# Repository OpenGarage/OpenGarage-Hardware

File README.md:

OpenGarage is a WiFi universal garage door opener based on the ESP8266 chip.

For details, visit [http://opengarage.io](http://opengarage.io)

This folder contains OpenGarage hardware design files, including:

* Schematic and Board files (EagleCAD)
* BOM, Pin assignments
* Enclosure design files
  - The original 3D design can be found at TinkerCad.com -> search for OpenGarage

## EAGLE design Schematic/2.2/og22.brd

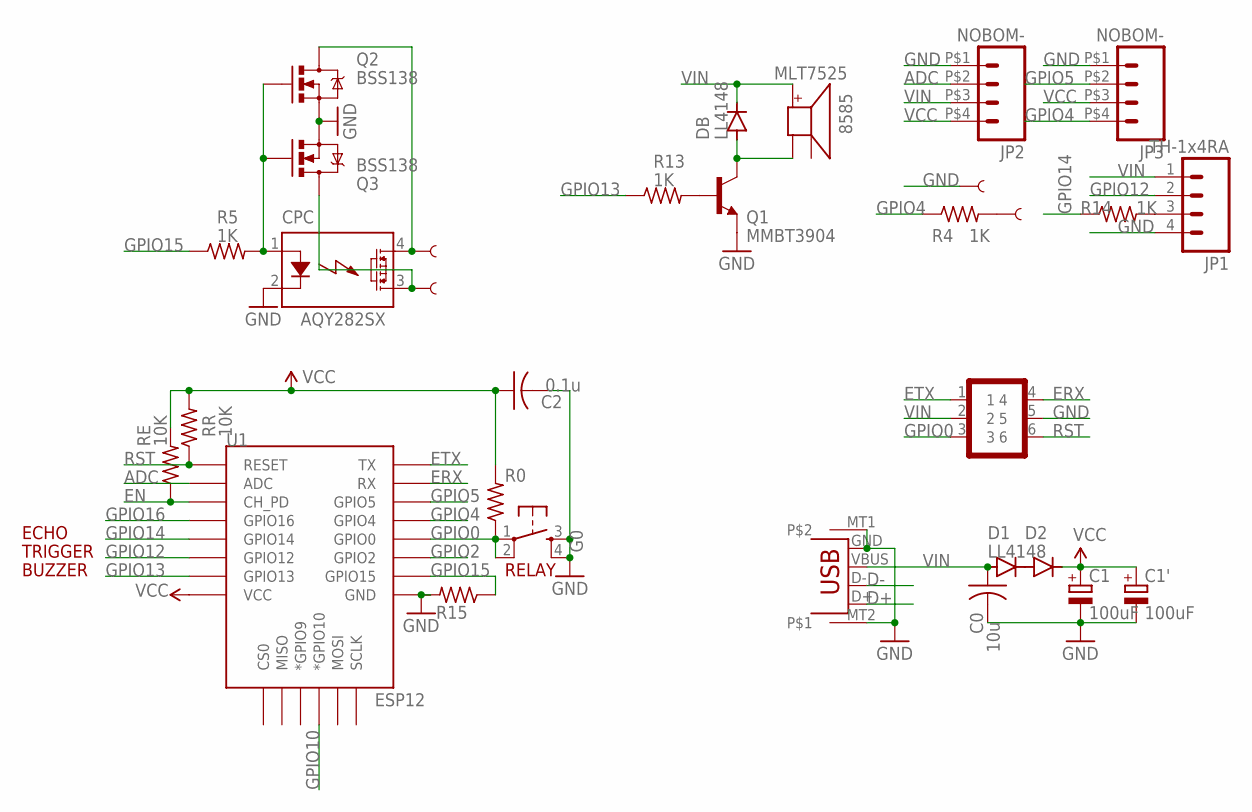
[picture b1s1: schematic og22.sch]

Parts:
8585: MLT7525; SMT-8585-BUZZER
C0: 10u; C0805K
C1, C1': 100uF; PANASONIC_C
C2: 0.1u; C0603K
CPC: AQY282SX; PHOTOMOS
D1, D2: LL4148; MINIMELF
DB: LL4148; MINIMELF
G0: TH-6x11; EVQ-Q2
JP1: TH-1x4RA; 1X04_SONICSENSOR_EXT2
JP2, JP3: NOBOM-; 1X04-2X2
Q1: MMBT3904; SOT23-3
Q2, Q3: BSS138; SOT23-3
R0, R15: 10K; R0603
R4, R5, R13, R14: 1K; R0603
RE: 10K; R0603
RR: 10K; R0603
U1: ESP12; ESP12E-SMD
U$1: NOBOM-GF2x3; GOLDFINGER_2X3
U$2, U$3, U$4, U$5: NOBOM-; PETAL-7MM-DOUBLE
X3: MICROXNJ; USB-MICROB2

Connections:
ADC: JP2.P$2 (2), U1.ADC
D+: X3.D+
D-: X3.D-
EN: RE.1, U1.CH_PD
ERX: U1.RXD0 (RX), U$1.4
ETX: U1.TXD0 (TX), U$1.1
GND: C0.2, C1.-, C1'.-, C2.2, CPC.2 (K), G0.3, G0.4, JP1.4, JP2.P$1 (1), JP3.P$1 (1), Q1.2 (E), Q2.2 (S), Q3.2 (S), R15.2, U1.GND, U$1.5, U$4.P$1, X3.GND, X3.MT1, X3.MT2
GPIO0: G0.1, G0.2, R0.1, U1.GPIO0, U$1.3
GPIO2: U1.GPIO2
GPIO4: JP3.P$4 (4), R4.1, U1.GPIO4
GPIO5: JP3.P$2 (2), U1.GPIO5
GPIO10: U1.GPIO10 (*GPIO10)
GPIO12: JP1.2, U1.GPIO12
GPIO13: R13.1, U1.GPIO13
GPIO14: R14.1, U1.GPIO14
GPIO15: R5.1, R15.1, U1.GPIO15
GPIO16: U1.GPIO16
unnamed: CPC.4 (DS1), Q2.3 (D), U$3.P$1
unnamed: CPC.3 (DS2), Q3.3 (D), U$2.P$1
unnamed: R4.2, U$5.P$1
unnamed: JP1.3, R14.2
unnamed: 8585.-, DB.A, Q1.3 (C)
unnamed: Q1.1 (B), R13.2
unnamed: CPC.1 (A), Q2.1 (G), Q3.1 (G), R5.2
unnamed: D1.C, D2.A
RST: RR.1, U1.RESET, U$1.6
VCC: C1.+, C1'.+, C2.1, D2.C, JP2.P$4 (4), JP3.P$3 (3), R0.2, RE.2, RR.2, U1.VCC
VIN: 8585.+, C0.1, D1.A, DB.C, JP1.1, JP2.P$3 (3), U$1.2, X3.VBUS

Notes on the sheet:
RELAY
BUZZER
ECHO
TRIGGER

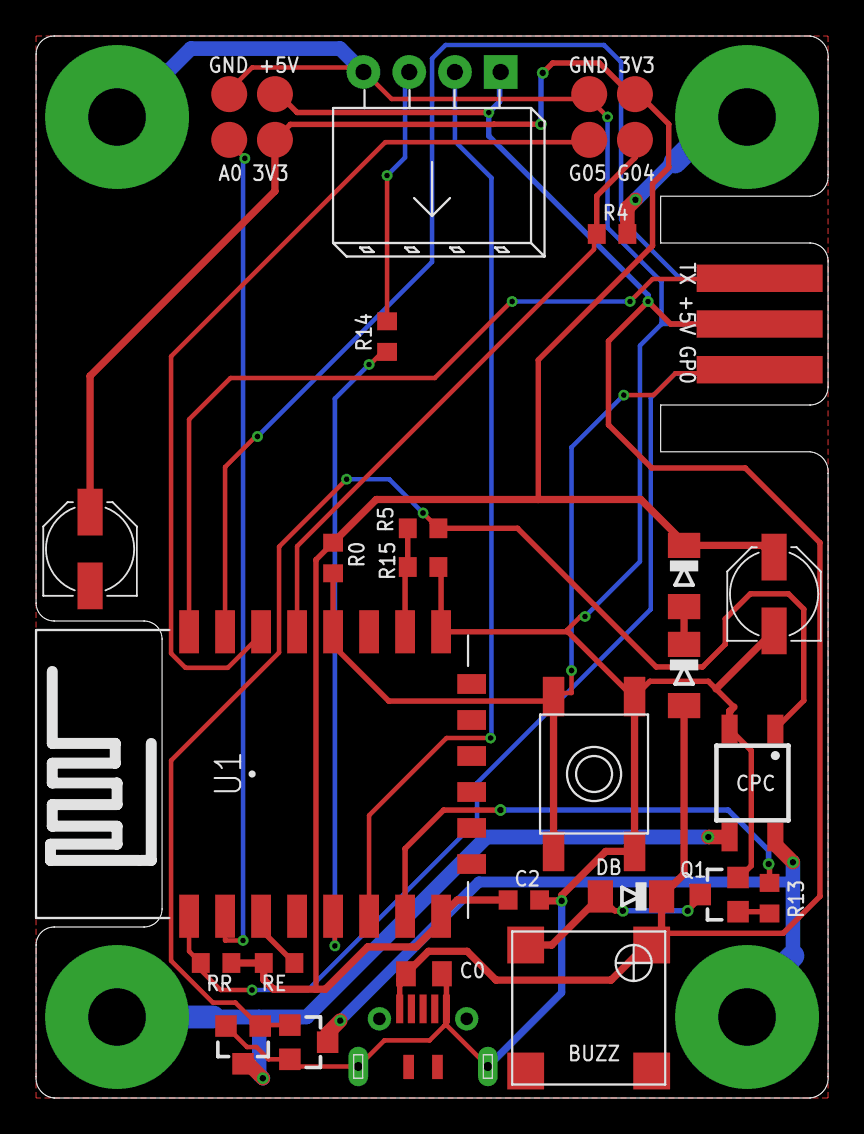
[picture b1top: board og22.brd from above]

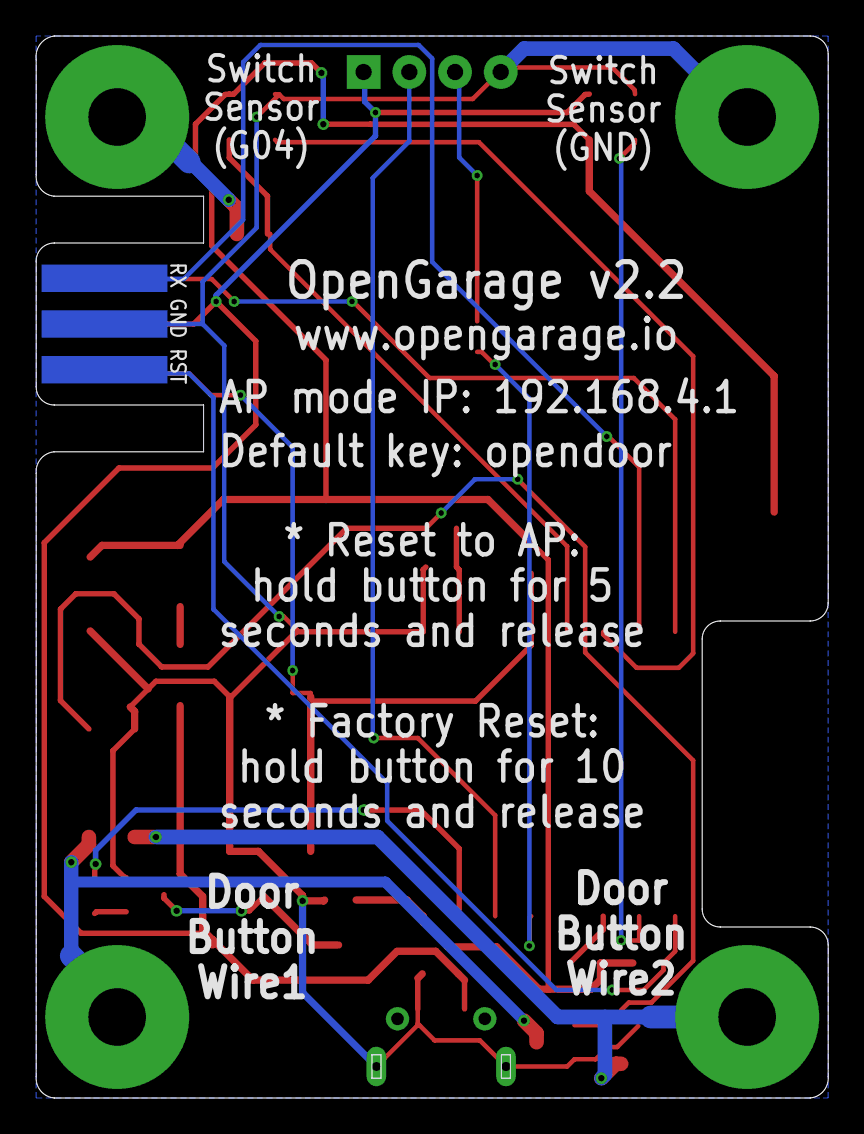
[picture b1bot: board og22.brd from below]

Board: 2 copper layers, 44.0 x 59.0 mm, 31 parts (4 on the bottom side), 23 nets.

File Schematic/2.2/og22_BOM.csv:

Name,Designator,Footprint,Quantity
0.1u,C2,C0603K,1
1K,"R4,R5,R13,R14",R0603,4
10K,"R0,R15,RE,RR",R0603,4
10u,C0,C0805K,1
100uF,"C1, C1'",PANASONIC_C,2
BSS138,Q2-3,SOT23-3,2
ESP12,U1,ESP12E-SMD,1
LL4148,"D1,D2,DB",MINIMELF,3
MICROXNJ,X3,USB-MICROB2,1
MLT7525,8585,SMT-8585-BUZZER,1
MMBT3904,Q1,SOT23-3,1
TH-1x4RA,JP1,1X04_SONICSENSOR_EXT2,1
TH-6x11,G0,EVQ-Q2,1

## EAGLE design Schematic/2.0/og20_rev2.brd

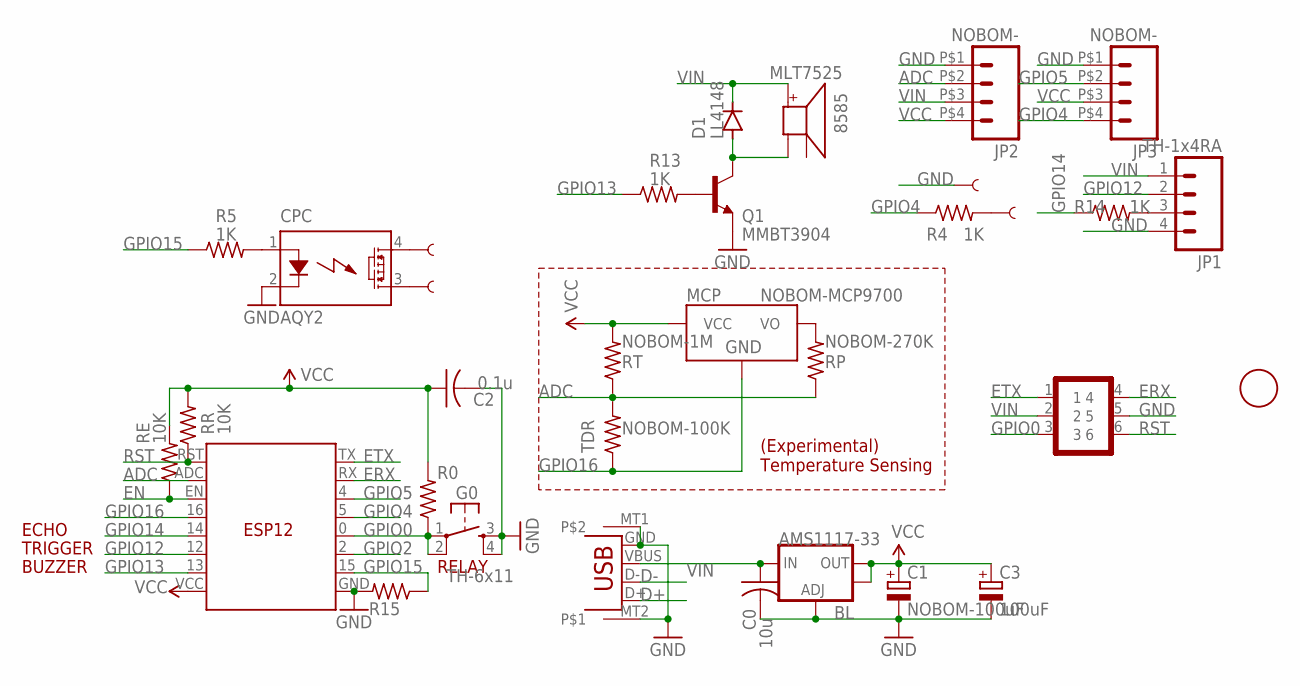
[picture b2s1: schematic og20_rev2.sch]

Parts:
0F: FIDUCIAL; FIDUCIAL_1MM
8585: MLT7525; SMT-8585-BUZZER
BL: AMS1117-33; SOT223
C0: 10u; C0805K
C1: NOBOM-100uF; B/3528-21R
C2: 0.1u; C0603K
C3: 100uF; PANASONIC_C
CPC: AQY2; PHOTOMOS
D1: LL4148; MINIMELF
ESP: ESP8266; ESP12
G0: TH-6x11; TACTILE-PTH
JP1: TH-1x4RA; 1X04_SONICSENSOR_EXT2
JP2, JP3: NOBOM-; 1X04-2X2
MCP: NOBOM-MCP9700; SOT23-3
Q1: MMBT3904; SOT23-3
R0, R15: 10K; R0603
R4, R5, R13, R14: 1K; R0603
RE: 10K; R0603
RP: NOBOM-270K; R0603
RR: 10K; R0603
RT: NOBOM-1M; R0603
TDR: NOBOM-100K; R0805
U$1: NOBOM-GF2x3; GOLDFINGER_2X3
U$2, U$3, U$4, U$5: NOBOM-; PETAL-3MM-1SIDE
X3: MICROXNJ; USB-MICROB2

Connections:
ADC: ESP.ADC, JP2.P$2 (2), RP.1, RT.1, TDR.2
D+: X3.D+
D-: X3.D-
EN: ESP.EN, RE.1
ERX: ESP.RX, U$1.4
ETX: ESP.TX, U$1.1
GND: BL.1 (ADJ), C0.2, C1.-, C2.2, C3.-, CPC.2 (K), ESP.GND, G0.3, G0.4, JP1.4, JP2.P$1 (1), JP3.P$1 (1), Q1.2 (E), R15.2, U$1.5, U$4.P$1, X3.GND, X3.MT1, X3.MT2
GPIO0: ESP.0 (G0), G0.1, G0.2, R0.1, U$1.3
GPIO2: ESP.2 (G2)
GPIO4: ESP.5 (G5), JP3.P$4 (4), R4.1
GPIO5: ESP.4 (G4), JP3.P$2 (2)
GPIO12: ESP.12 (G12), JP1.2
GPIO13: ESP.13 (G13), R13.1
GPIO14: ESP.14 (G14), R14.1
GPIO15: ESP.15 (G15), R5.1, R15.1
GPIO16: ESP.16 (G16), MCP.3 (GND), TDR.1
unnamed: CPC.4 (DS1), U$2.P$1
unnamed: CPC.3 (DS2), U$3.P$1
unnamed: R4.2, U$5.P$1
unnamed: JP1.3, R14.2
unnamed: 8585.-, D1.A, Q1.3 (C)
unnamed: MCP.2 (VO), RP.2
unnamed: Q1.1 (B), R13.2
unnamed: CPC.1 (A), R5.2
RST: ESP.RST, RR.1, U$1.6
VCC: BL.2 (OUT), BL.4 (OUT), C1.+, C2.1, C3.+, ESP.VCC, JP2.P$4 (4), JP3.P$3 (3), MCP.1 (VCC), R0.2, RE.2, RR.2, RT.2
VIN: 8585.+, BL.3 (IN), C0.1, D1.C, JP1.1, JP2.P$3 (3), U$1.2, X3.VBUS

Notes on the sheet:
RELAY
BUZZER
ECHO
TRIGGER
(Experimental) Temperature Sensing

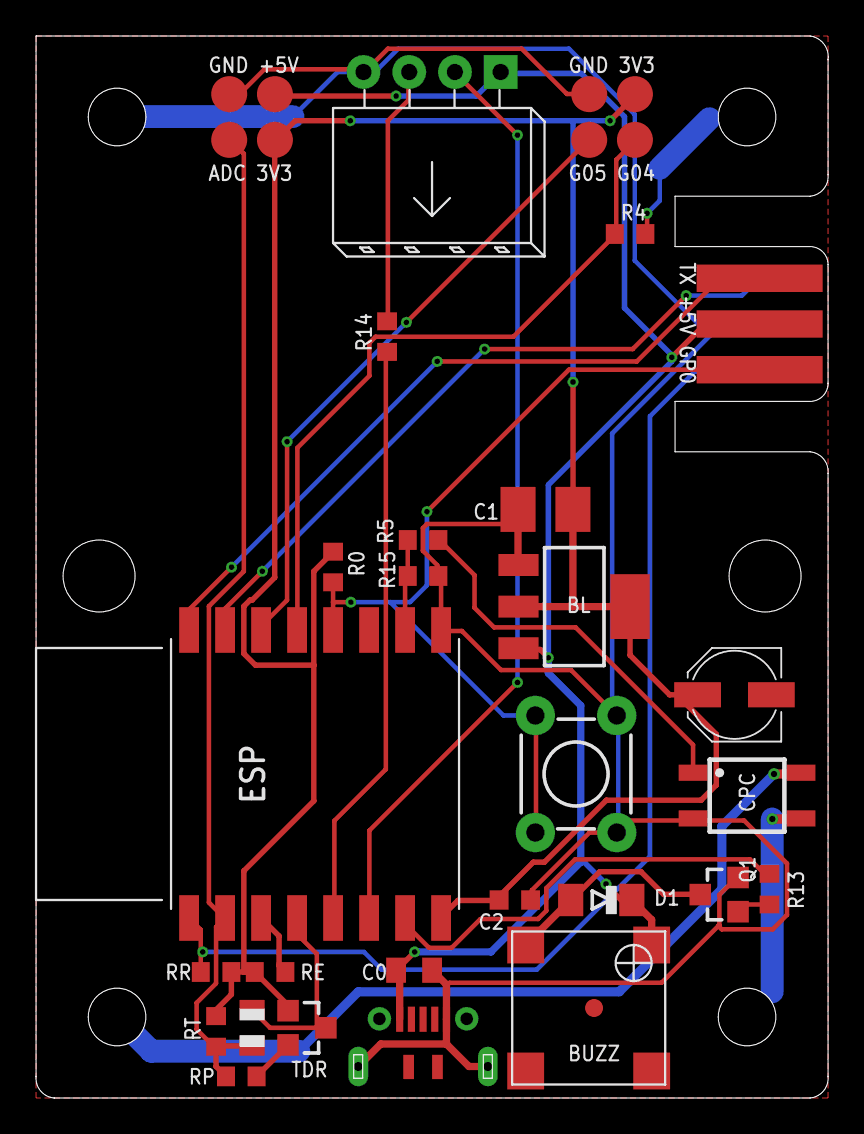
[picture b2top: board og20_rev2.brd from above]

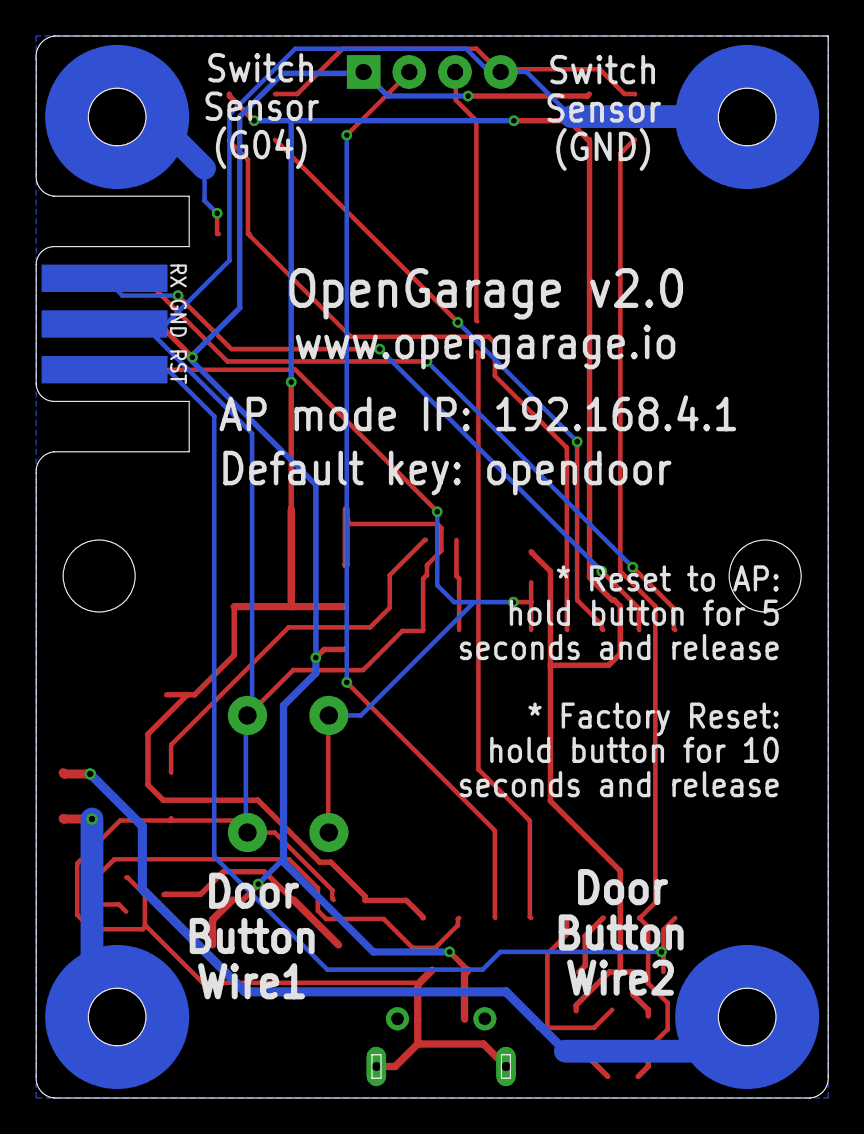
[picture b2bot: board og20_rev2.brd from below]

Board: 2 copper layers, 44.0 x 59.0 mm, 33 parts (4 on the bottom side), 24 nets.

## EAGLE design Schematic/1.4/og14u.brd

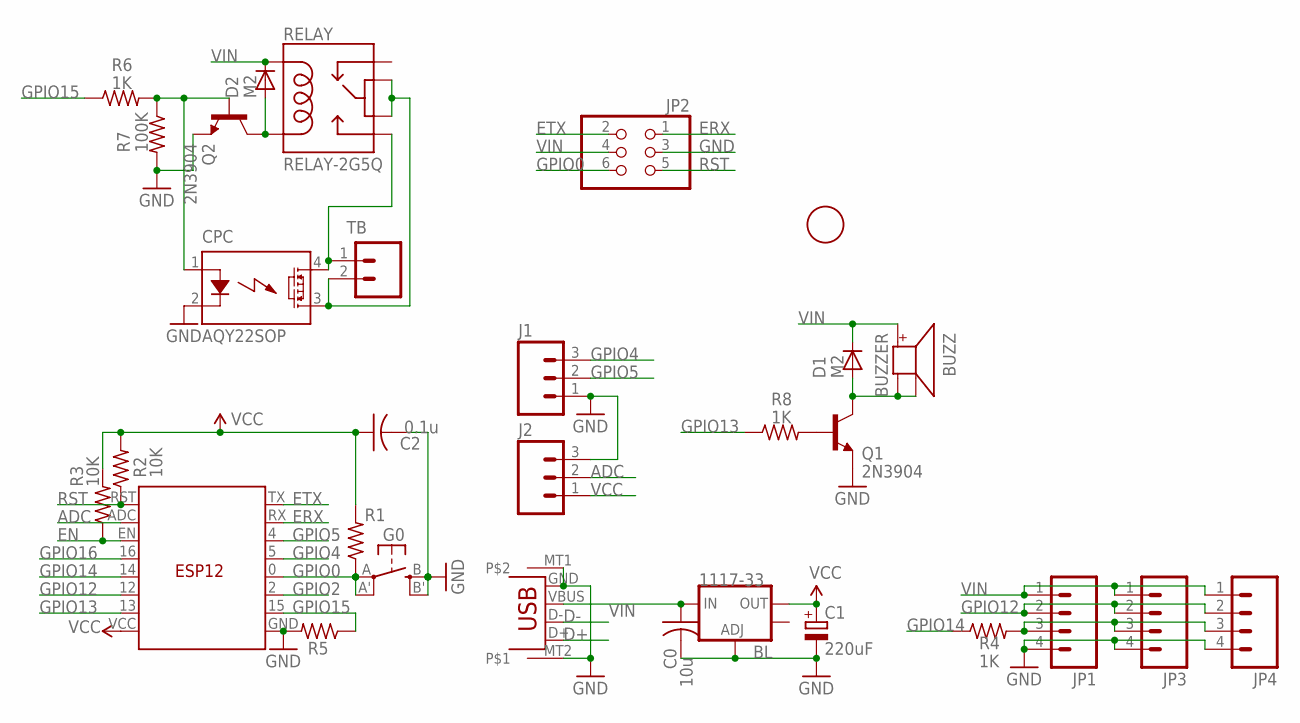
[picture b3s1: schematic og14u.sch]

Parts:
1F: FIDUCIAL; FIDUCIAL_1MM
BL: 1117-33; SOT223
BUZZ: BUZZER; SMT-8585-BUZZER
C0: 10u; C0805K
C1: 220uF; B/3528-21R
C2: 0.1u; C0603K
CPC: AQY22SOP; SOP04
D1, D2: M2; DO-214AC
ESP: ESP12
G0: SPST_TACT-EVQQ2; EVQ-Q2
J1, J2: M03PTH; 1X03
JP1: M04SONICSMD; 1X04_SONICSENSOR_SMD
JP2: PINHD-2X3; 2X03
JP3, JP4: M04DIST; 1X04_NO_SILK_DIST
Q1, Q2: 2N3904; SOT23-3
R1, R2, R3, R5: 10K; R0603
R4, R6, R8: 1K; R0603
R7: 100K; R0603
RELAY: RELAY-2G5Q; RELAY-G5V
TB: OPENER; SCREWTERMINAL-5MM-2-KF
X3: USB+GND; USB-MICROB2

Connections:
ADC: ESP.ADC, J2.2
D+: X3.D+
D-: X3.D-
EN: ESP.EN, R3.1
ERX: ESP.RX, JP2.1
ETX: ESP.TX, JP2.2
GND: BL.1 (ADJ), C0.2, C1.-, C2.2, CPC.2 (K), ESP.GND, G0.B (S), G0.B' (S1), J1.1, J2.3, JP1.4, JP2.3, JP3.4, JP4.4, Q1.2 (E), Q2.2 (E), R5.2, R7.2, X3.GND, X3.MT1, X3.MT2
GPIO0: ESP.0 (G0), G0.A, G0.A' (P1), JP2.6, R1.1
GPIO2: ESP.2 (G2)
GPIO4: ESP.5 (G5), J1.3
GPIO5: ESP.4 (G4), J1.2
GPIO12: ESP.12 (G12), JP1.2, JP3.2, JP4.2
GPIO13: ESP.13 (G13), R8.1
GPIO14: ESP.14 (G14), R4.1
GPIO15: ESP.15 (G15), R5.1, R6.1
GPIO16: ESP.16 (G16)
unnamed: CPC.4 (DS1), RELAY.10, TB.1
unnamed: CPC.3 (DS2), RELAY.5, RELAY.6, TB.2
unnamed: JP1.3, JP3.3, JP4.3, R4.2
unnamed: BUZZ.-, BUZZ.A-, D1.A, Q1.3 (C)
unnamed: Q1.1 (B), R8.2
unnamed: D2.A, Q2.3 (C), RELAY.9
unnamed: CPC.1 (A), Q2.1 (B), R6.2, R7.1
RST: ESP.RST, JP2.5, R2.1
VCC: BL.2 (OUT), C1.+, C2.1, ESP.VCC, J2.1, R1.2, R2.2, R3.2
VIN: BL.3 (IN), BUZZ.+, C0.1, D1.C, D2.C, JP1.1, JP2.4, JP3.1, JP4.1, RELAY.2, X3.VBUS

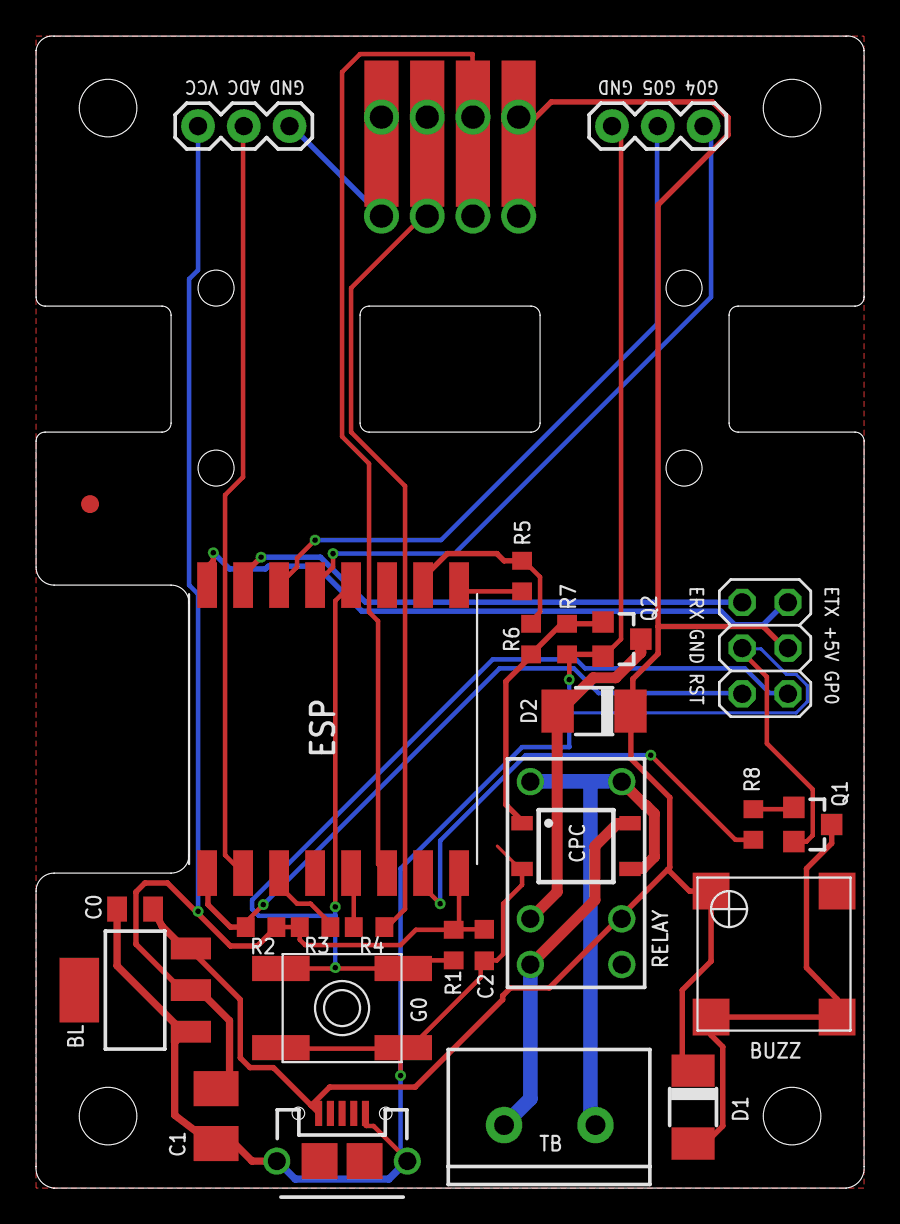
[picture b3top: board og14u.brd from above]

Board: 2 copper layers, 46.0 x 64.0 mm, 30 parts (0 on the bottom side), 22 nets.

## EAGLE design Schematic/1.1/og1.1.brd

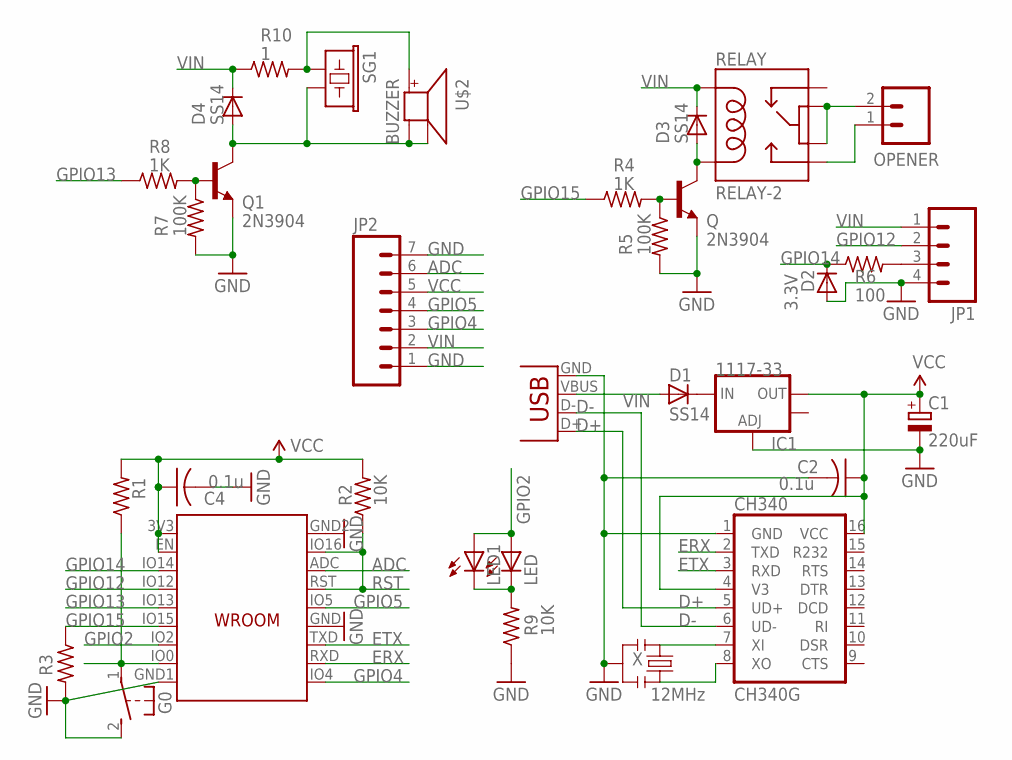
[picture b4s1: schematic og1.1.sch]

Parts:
C1: 220uF; CT3528
C2, C4: 0.1u; C0603K
CH340: CH340G; SO16
D1, D3, D4: SS14; DO-214AC
D2: 3.3V; MINIMELF
ESP: WROOM02; WROOM
G0: 31-XX; B3F-31XX
IC1: 1117-33; SOT223
JP1: M04SONIC; 1X04_SONICSENSOR
JP2: M07; 1X07
LED: LEDLED3MM_ABBRV; LED3MM_ABBRV
LED1: LEDCHIPLED_0805; CHIPLED_0805
OPENER: OPENER; SCREWTERMINAL-4MM-2-X
Q, Q1: 2N3904; SOT23-3
R1, R2, R3, R9: 10K; R0603
R4, R8: 1K; R0603
R5, R7: 100K; R0603
R6: 100; R0603
R10: 1; R0603
RELAY: RELAY-2; RELAY-HK4100F
SG1: BUZZERPTH; BUZZER-12MM
U$2: BUZZER; SMT-8585-BUZZER
X: 12MHz; RESONATOR-SMD
X3: USB-MICROB

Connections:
ADC: ESP.ADC, JP2.6
D+: CH340.5 (UD+), X3.D+
D-: CH340.6 (UD-), X3.D-
ERX: CH340.2 (TXD), ESP.RXD (RX)
ETX: CH340.3 (RXD), ESP.TXD (TX)
GND: C1.-, C2.2, C4.2, CH340.1 (GND), D2.A, ESP.GND, ESP.GND1, ESP.GND2, G0.2 (S), IC1.1 (ADJ), JP1.4, JP2.1, JP2.7, Q.2 (E), Q1.2 (E), R3.2, R5.2, R7.2, R9.1, X.2, X3.GND
GPIO0: ESP.IO0, G0.1, R1.1
GPIO2: ESP.IO2, LED.A, LED1.A
GPIO4: ESP.IO4, JP2.3
GPIO5: ESP.IO5, JP2.4
GPIO12: ESP.IO12, JP1.2
GPIO13: ESP.IO13, R8.1
GPIO14: D2.C, ESP.IO14, R6.1
GPIO15: ESP.IO15, R3.1, R4.1
unnamed: D1.C, IC1.3 (IN)
unnamed: Q.1 (B), R4.2, R5.1
unnamed: OPENER.2, RELAY.5, RELAY.6
unnamed: OPENER.1, RELAY.10
unnamed: JP1.3, R6.2
unnamed: D4.A, Q1.3 (C), SG1.- (2), U$2.-, U$2.A-
unnamed: LED.K (C), LED1.C, R9.2
unnamed: Q1.1 (B), R7.1, R8.2
unnamed: R10.2, SG1.+ (1), U$2.+
unnamed: CH340.7 (XI), X.1
unnamed: CH340.8 (XO), X.3
unnamed: D3.A, Q.3 (C), RELAY.9
RST: ESP.IO16, ESP.RST, R2.1
VCC: C1.+, C2.1, C4.1, CH340.4 (V3), CH340.16 (VCC), ESP.3V3 (VCC), ESP.EN, IC1.2 (OUT), JP2.5, R1.2, R2.2
VIN: D1.A, D3.C, D4.C, JP1.1, JP2.2, R10.1, RELAY.2, X3.VBUS

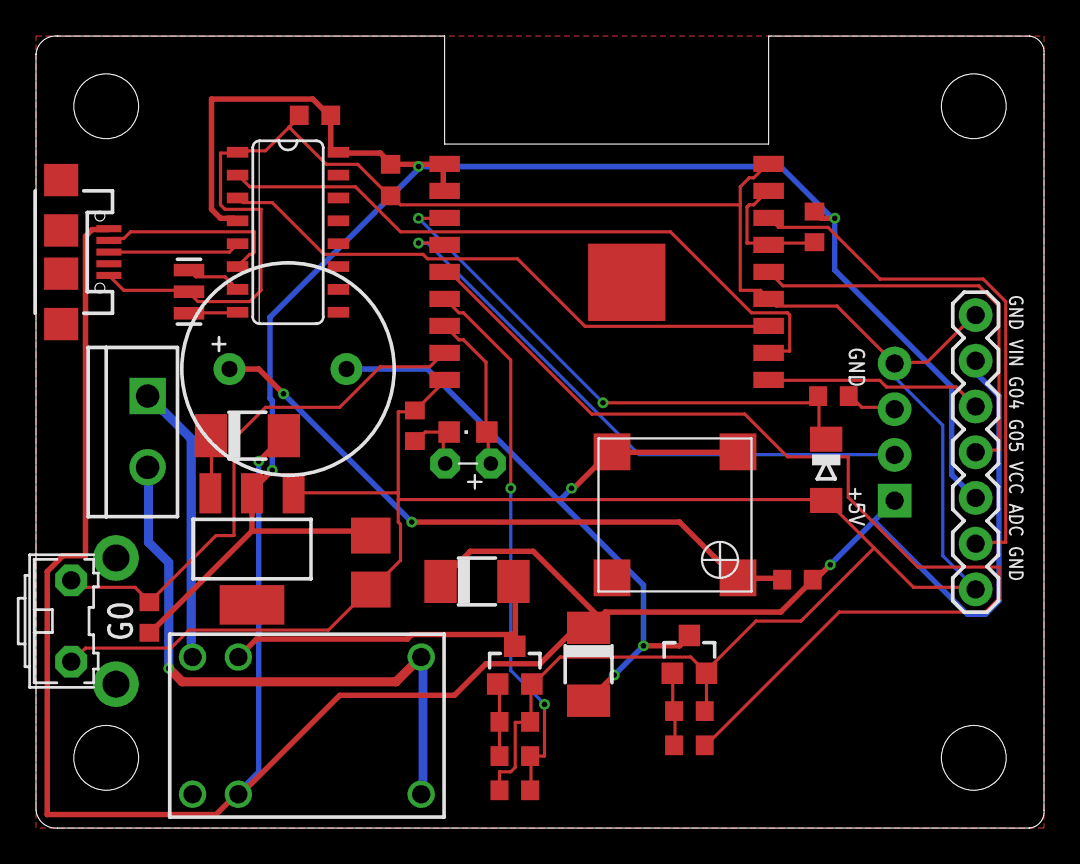
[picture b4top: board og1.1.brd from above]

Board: 2 copper layers, 56.0 x 44.0 mm, 33 parts (0 on the bottom side), 29 nets.

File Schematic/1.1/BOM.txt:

Part List

Part   Value      Device                Package               Description                          

C1     220uF      CPOL-EUCT3528         CT3528                POLARIZED CAPACITOR, European symbol 
C2     0.1u       C-USC0603K            C0603K                CAPACITOR, American symbol           
C4     0.1u       C-USC0603K            C0603K                CAPACITOR, American symbol           
CH340  CH340G     CH340G                SO16                                                       
D1     SS14       DIODE-DO-214AC        DO-214AC              DIODE                                
D2     3.3V       DIODE-MINIMELF        MINIMELF              DIODE                                
D3     SS14       DIODE-DO-214AC        DO-214AC              DIODE                                
D4     SS14       DIODE-DO-214AC        DO-214AC              DIODE                                
ESP    WROOM02    WROOM02               WROOM                                                      
G0                31-XX                 B3F-31XX              OMRON SWITCH                         
IC1    1117-33    V_REG_LM1117SOT223    SOT223                Voltage Regulator LM1117             
JP1    ULTRASONIC HC-SR04               HC-SR04                          
LED               LEDLED3MM_ABBRV       LED3MM_ABBRV          LED                                  
LED1              LEDCHIPLED_0805       CHIPLED_0805          LED                                  
OPENER OPENER     M024MM-X              SCREWTERMINAL-4MM-2-X Header 2                             
Q      2N3904     TRANSISTOR_NPNSOT23-3 SOT23-3               Transistor NPN                       
Q1     2N3904     TRANSISTOR_NPNSOT23-3 SOT23-3               Transistor NPN                       
R1     10K        R-US_R0603            R0603                 RESISTOR, American symbol            
R2     10K        R-US_R0603            R0603                 RESISTOR, American symbol            
R3     10K        R-US_R0603            R0603                 RESISTOR, American symbol            
R4     1K         R-US_R0603            R0603                 RESISTOR, American symbol            
R5     100K       R-US_R0603            R0603                 RESISTOR, American symbol            
R6     100        R-US_R0603            R0603                 RESISTOR, American symbol            
R7     100K       R-US_R0603            R0603                 RESISTOR, American symbol            
R8     1K         R-US_R0603            R0603                 RESISTOR, American symbol            
R9     10K        R-US_R0603            R0603                 RESISTOR, American symbol            
R10    1          R-US_R0603            R0603                 RESISTOR, American symbol            
RELAY  RELAY-2    HK4100F-5VDC          HK4100F-5VDC                                            
SG1               BUZZERPTH             BUZZER-12MM           Buzzer 12mm                          
U$2    BUZZER     BUZZER                SMT-8585-BUZZER                                            
X      12MHz      RESONATORSMD          RESONATOR-SMD         Resonator                            
X3     USB-MICROB USB-MICROB            USB-MICROB            USB Connectors

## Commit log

2016-03-12 check in schematic and enclosure design files
2016-03-13 changing url and adding A0 to PINS.txt
2016-03-13 change url
2016-09-02 check in updated schematic
2016-10-01 update pin definitions
2018-12-21 Fixed typos
2020-09-12 add version 1.4 Eagle files
2021-05-06 add OG 2.0 schematic, bom, and enclosure design
2021-05-06 re-structure enclosure folder
2024-12-16 add version 2.2 hardware design files
2025-10-07 add 2.3+ design files. update license

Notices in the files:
parts and their libraries:
SparkFunNew: Licensing: CC v3.0 Share-Alike You are welcome to use this library for commercial purposes.
